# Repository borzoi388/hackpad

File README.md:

# Fishpad
Fishpad is the 9-key fish-shaped macropad of my dreams with an OLED display and a rotary encoder. Uses QMK firmware and it will have VIA support C:

## Features:

- 9 switches and a rotary encoder! (sadly no click on the encoder :c)
- 128x32 OLED screen
- LED underglow
- Case that's supposed to look like a fish?

## Case: 

Sandwich mount! Made in Onshape. The case has 3 parts, a bottom, plate for the keys, and a top. (all different colors in the picture :D). Also has a fun mouth-shaped usb cutout.

## PCB:

Schematic

PCB

Made with <3 in Kicad. Silkscreen imported from Figma. Time spent on the pcb was journaled 

## Firmware:

- Used QMK and used adafruit/macropad as a template since it had similar features to mine
- Not entirely finished, I will be using VIA to change the macros and leds
- I did add two layers of macros for now, one for gaming and one for drawing. Will probably change in the future!

# BOM:

    1x Seeed XIAO RP2040
    9x through-hole 1N4148 Diodes
    9x MX-Style switches
    1x EC11 Rotary encoders
    1x 0.91 inch OLED display
    9x white blank DSA keycaps
    9x SK6812 MINI-E LEDs
    4x M3x16mm screws
    1x Case (three 3d printed parts)

yup i copied this from hackpad website

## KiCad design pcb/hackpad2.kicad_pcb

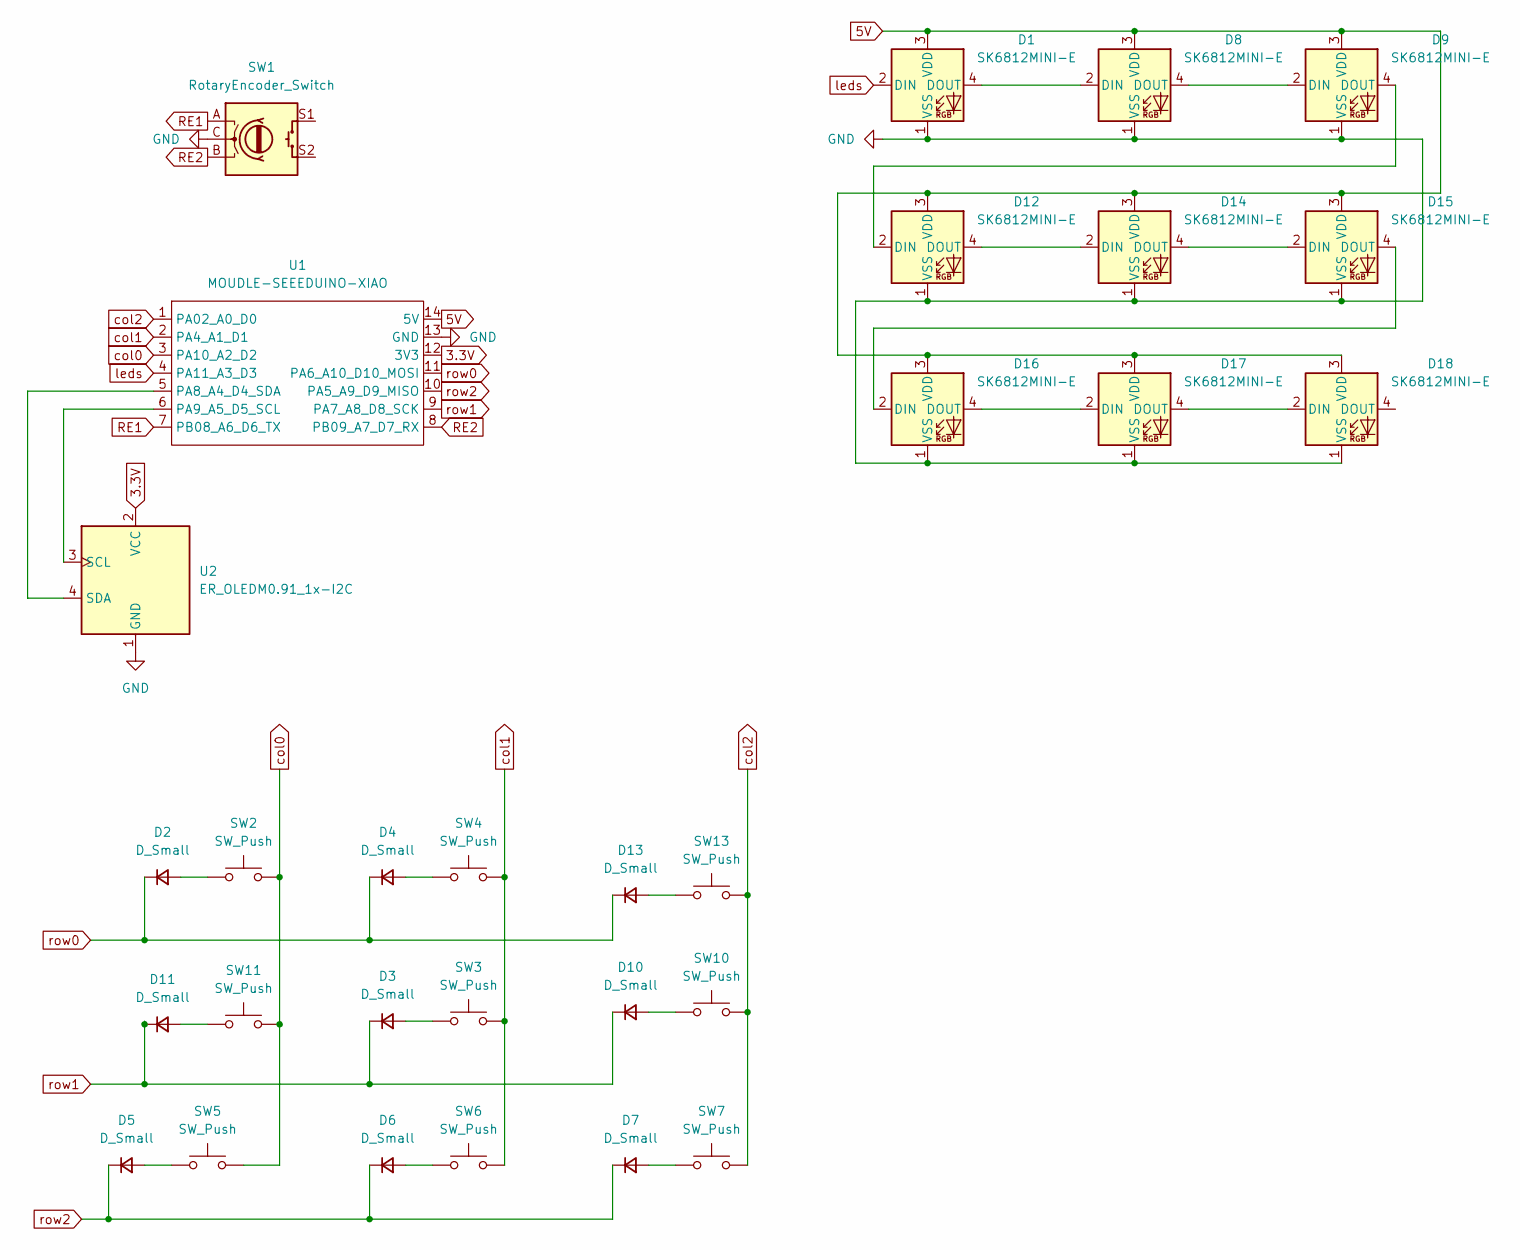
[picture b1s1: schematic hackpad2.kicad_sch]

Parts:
D1, D8, D9, D12, D14, D15, D16, D17, D18: SK6812MINI-E; LED_SK6812MINI-E_3.2x2.8mm_P1.5mm_ReverseMount
D2, D3, D4, D5, D6, D7, D10, D11, D13: D_Small; D_DO-35_SOD27_P7.62mm_Horizontal
SW1: RotaryEncoder_Switch; RotaryEncoder_Alps_EC11E-Switch_Vertical_H20mm
SW2, SW3, SW4, SW5, SW6, SW7, SW10, SW11, SW13: SW_Push; SW_Cherry_MX_1.00u_PCB
U1: MOUDLE-SEEEDUINO-XIAO; XIAO-Generic-Hybrid-14P-2.54-21X17.8MM
U2: ER_OLEDM0.91_1x-I2C

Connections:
3.3V: U1.12 (3V3), U2.2 (VCC)
5V: D1.3 (VDD), D8.3 (VDD), D9.3 (VDD), D12.3 (VDD), D14.3 (VDD), D15.3 (VDD), D16.3 (VDD), D17.3 (VDD), D18.3 (VDD), U1.14 (5V)
GND: D1.1 (VSS), D8.1 (VSS), D9.1 (VSS), D12.1 (VSS), D14.1 (VSS), D15.1 (VSS), D16.1 (VSS), D17.1 (VSS), D18.1 (VSS), SW1.C, U1.13 (GND), U2.1 (GND)
unnamed: D1.4 (DOUT), D8.2 (DIN)
unnamed: D2.2 (A), SW2.1
unnamed: D3.2 (A), SW3.1
unnamed: D4.2 (A), SW4.1
unnamed: D5.2 (A), SW5.1
unnamed: D6.2 (A), SW6.1
unnamed: D7.2 (A), SW7.1
unnamed: D8.4 (DOUT), D9.2 (DIN)
unnamed: D10.2 (A), SW10.1
unnamed: D11.2 (A), SW11.1
unnamed: D9.4 (DOUT), D12.2 (DIN)
unnamed: D12.4 (DOUT), D14.2 (DIN)
unnamed: D13.2 (A), SW13.1
unnamed: D14.4 (DOUT), D15.2 (DIN)
unnamed: D15.4 (DOUT), D16.2 (DIN)
unnamed: D16.4 (DOUT), D17.2 (DIN)
unnamed: D17.4 (DOUT), D18.2 (DIN)
unnamed: U1.5 (PA8_A4_D4_SDA), U2.4 (SDA)
unnamed: U1.6 (PA9_A5_D5_SCL), U2.3 (SCL)
RE1: SW1.A, U1.7 (PB08_A6_D6_TX)
RE2: SW1.B, U1.8 (PB09_A7_D7_RX)
col0: SW2.2, SW5.2, SW11.2, U1.3 (PA10_A2_D2)
col1: SW3.2, SW4.2, SW6.2, U1.2 (PA4_A1_D1)
col2: SW7.2, SW10.2, SW13.2, U1.1 (PA02_A0_D0)
leds: D1.2 (DIN), U1.4 (PA11_A3_D3)
row0: D2.1 (K), D4.1 (K), D13.1 (K), U1.11 (PA6_A10_D10_MOSI)
row1: D3.1 (K), D10.1 (K), D11.1 (K), U1.9 (PA7_A8_D8_SCK)
row2: D5.1 (K), D6.1 (K), D7.1 (K), U1.10 (PA5_A9_D9_MISO)

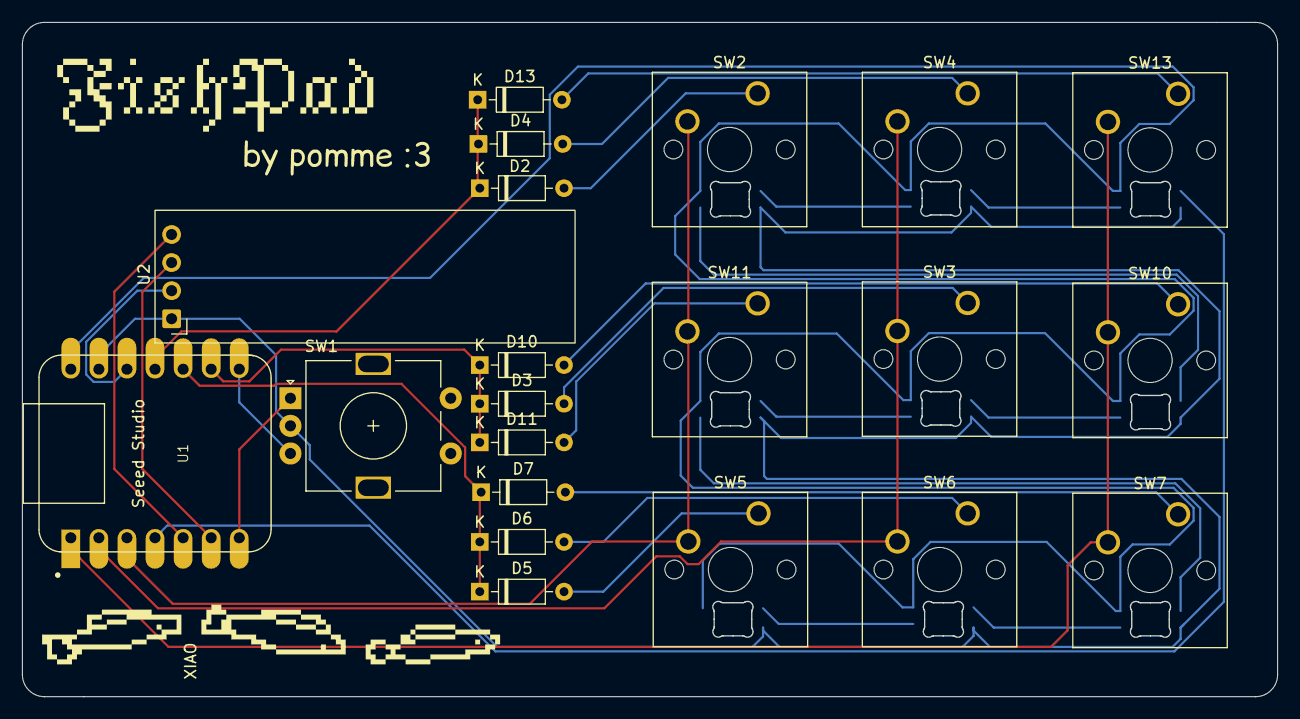
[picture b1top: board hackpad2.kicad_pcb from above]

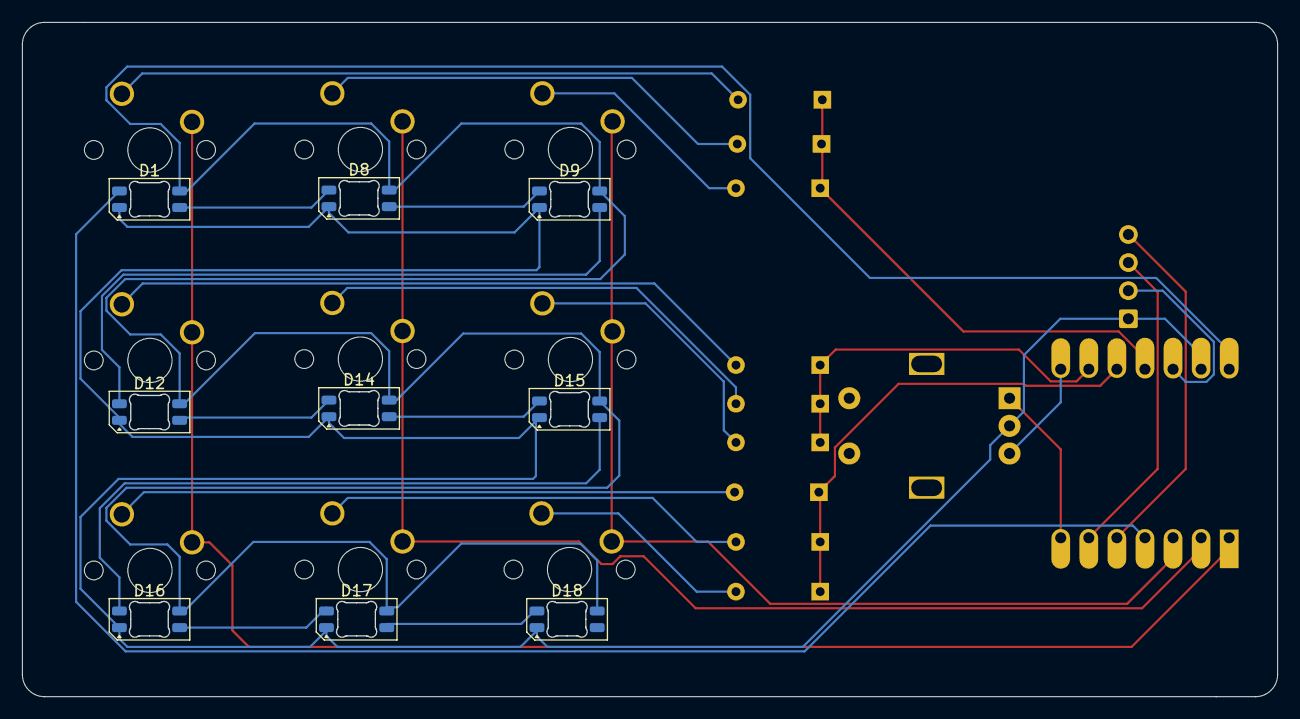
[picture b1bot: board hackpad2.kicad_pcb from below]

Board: 2 copper layers, 113.5 x 60.9 mm, 30 parts (9 on the bottom side), 31 nets.

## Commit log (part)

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2026-06-26 oled
2026-06-26 keys and fixing some structural stuff, surely this won't cause any problems
2026-06-26 journal 1
2026-06-29 schematic done?
2026-06-29 routing
